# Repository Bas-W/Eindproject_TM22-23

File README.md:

# eindprojectTM22_23
In dit project maken we een line following robot.
Je vindt in deze repository de bestanden om met een 3D printer de nodige stukken te vervaardigen alsook de code en een pdf waarin uitgelegd wordt hoe de hardware moet worden gemonteerd.

Hoe de server moet worden opgezet wordt niet uitgelegd.

Het project maakt gebruik van MQTT om te communiceren tussen de server en de robot. De robot stuurt data naar de server via MQTT, deze data wordt dan in een influxDB database gezet door een python script. De data kan dan weergegeven worden in een Grafana webpagina. De robot kan ook bediend worden vanuit de webpagina via MQTT berichten.

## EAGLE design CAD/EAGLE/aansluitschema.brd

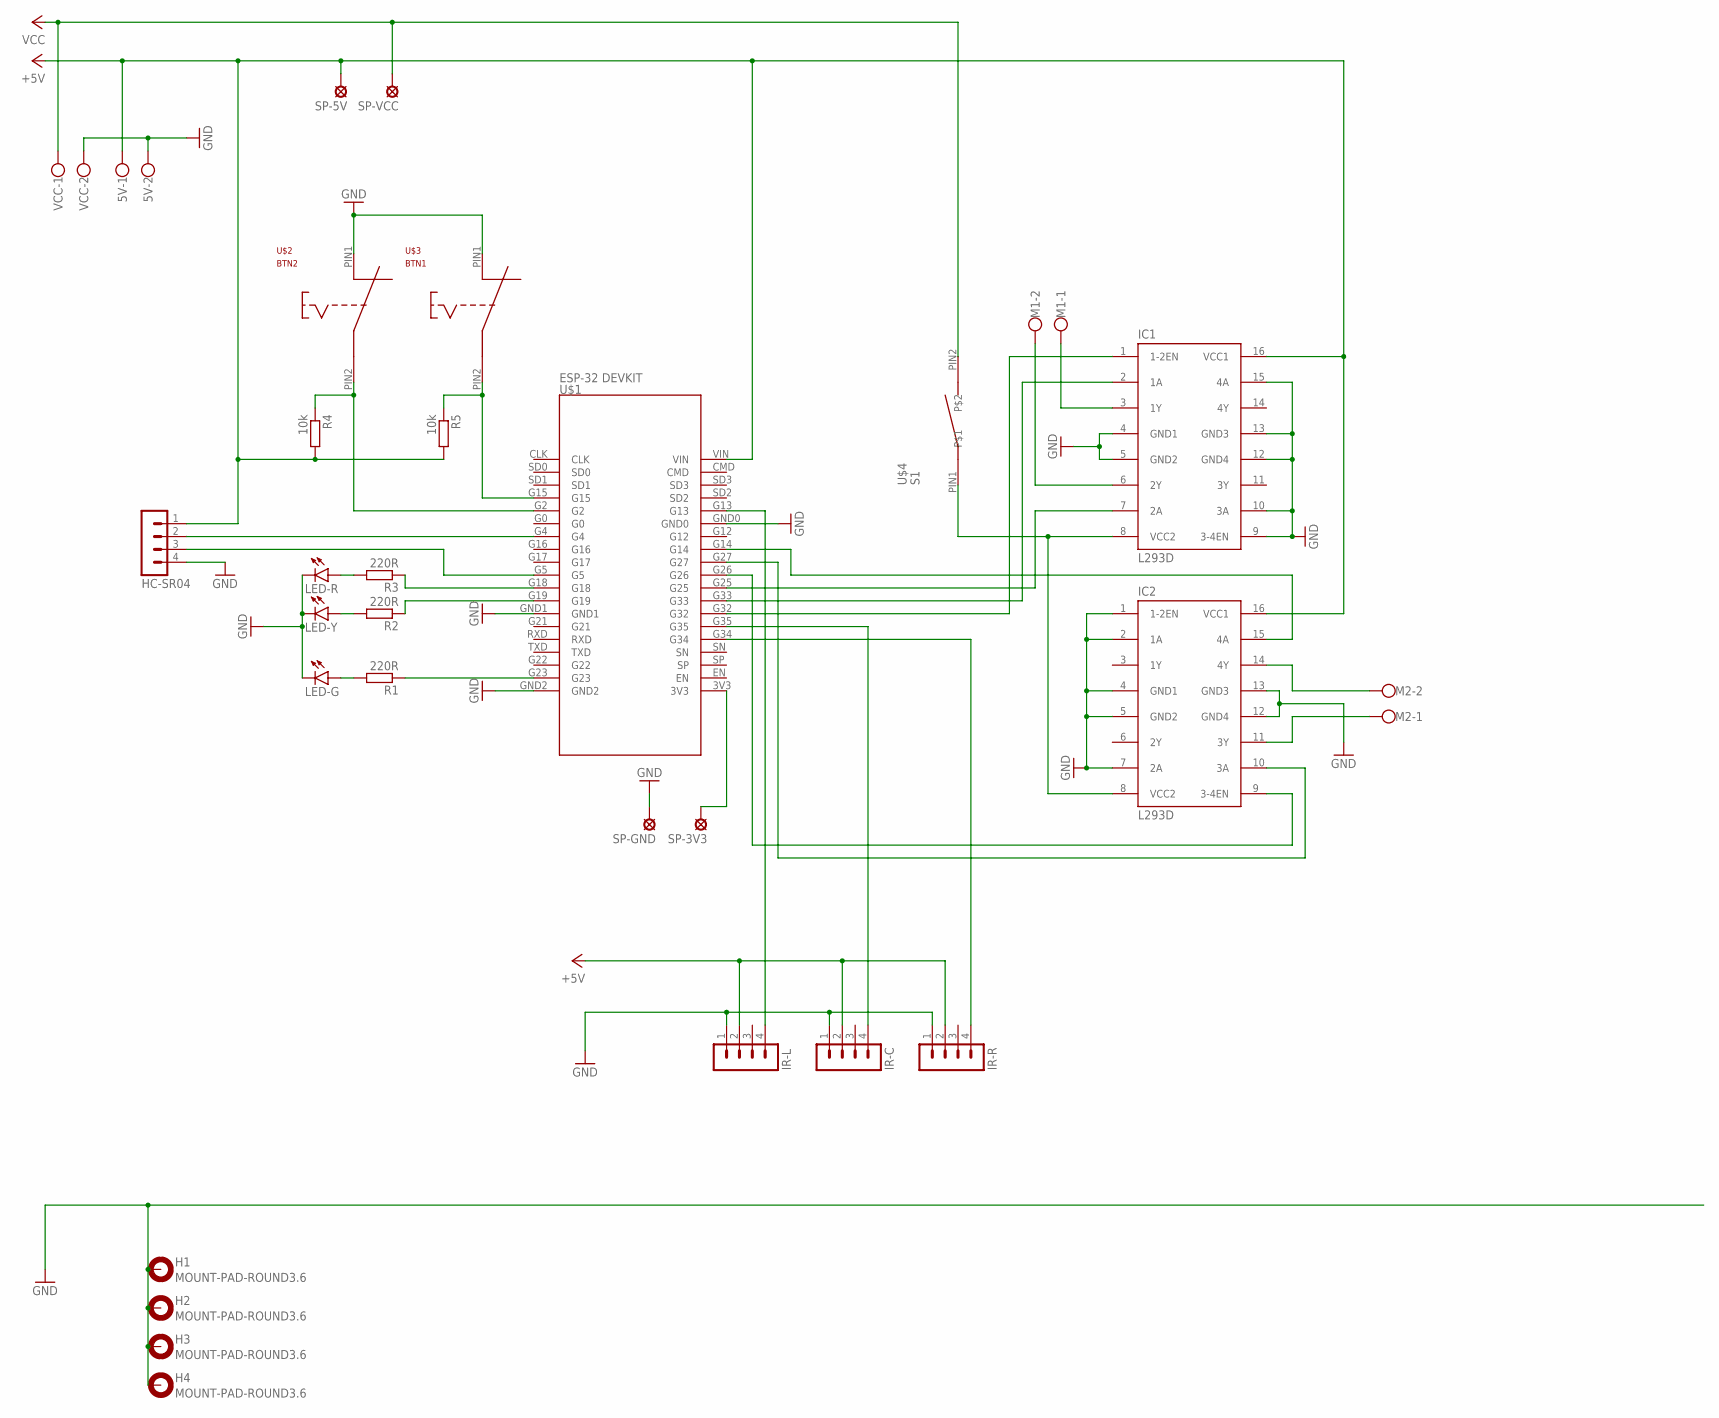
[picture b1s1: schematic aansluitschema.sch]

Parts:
5V: W237-102
H1, H2, H3, H4: MOUNT-PAD-ROUND3.6; 3,6-PAD
HC-SR04: MA04-1
IC1, IC2: L293D; DIL16
IR-C: MA04-1
IR-L: MA04-1
IR-R: MA04-1
LED-G: LED5MM
LED-R: LED5MM
LED-Y: LED5MM
M1, M2: W237-102
R1, R2, R3: 220R; 0207/10
R4, R5: 10k; 0207/10
SP-3V3, SP-5V: LSP10
SP-GND: LSP10
SP-VCC: LSP10
U$1: ESP-32 DEVKIT; ESP-32_DEVKIT
U$2: BTN2; PUSHBUTTON
U$3: BTN1; PUSHBUTTON
U$4: S1; SWITCH
VCC: W237-102

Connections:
+5V: 5V.1, HC-SR04.1, IC1.16 (VCC1), IC2.16 (VCC1), IR-C.2, IR-L.2, IR-R.2, R4.2, R5.2, SP-5V.MP, U$1.VIN
GND: 5V.2, H1.B3,6, H2.B3,6, H3.B3,6, H4.B3,6, HC-SR04.4, IC1.4 (GND1), IC1.5 (GND2), IC1.9 (3-4EN), IC1.10 (3A), IC1.12 (GND4), IC1.13 (GND3), IC1.15 (4A), IC2.1 (1-2EN), IC2.2 (1A), IC2.4 (GND1), IC2.5 (GND2), IC2.7 (2A), IC2.12 (GND4), IC2.13 (GND3), IR-C.1, IR-L.1, IR-R.1, LED-G.K (C), LED-R.K (C), LED-Y.K (C), SP-GND.MP, U$1.GND0, U$1.GND1, U$1.GND2, U$2.PIN1, U$3.PIN1, VCC.2
unnamed: IC1.8 (VCC2), IC2.8 (VCC2), U$4.PIN1
unnamed: LED-G.A, R1.2
unnamed: LED-Y.A, R2.2
unnamed: LED-R.A, R3.2
unnamed: R2.1, U$1.G19
unnamed: R3.1, U$1.G18
unnamed: R1.1, U$1.G23
unnamed: IR-R.4, U$1.G34
unnamed: IR-C.4, U$1.G35
unnamed: IR-L.4, U$1.G13
unnamed: HC-SR04.3, U$1.G5
unnamed: HC-SR04.2, U$1.G4
unnamed: R4.1, U$1.G2, U$2.PIN2
unnamed: R5.1, U$1.G15, U$3.PIN2
unnamed: IC1.3 (1Y), M1.1
unnamed: IC1.6 (2Y), M1.2
unnamed: IC2.11 (3Y), M2.1
unnamed: IC2.14 (4Y), M2.2
unnamed: IC1.1 (1-2EN), U$1.G32
unnamed: IC1.2 (1A), U$1.G33
unnamed: IC1.7 (2A), U$1.G25
unnamed: IC2.9 (3-4EN), U$1.G26
unnamed: IC2.10 (3A), U$1.G27
unnamed: IC2.15 (4A), U$1.G14
unnamed: SP-3V3.MP, U$1.3V3
VCC: SP-VCC.MP, U$4.PIN2, VCC.1

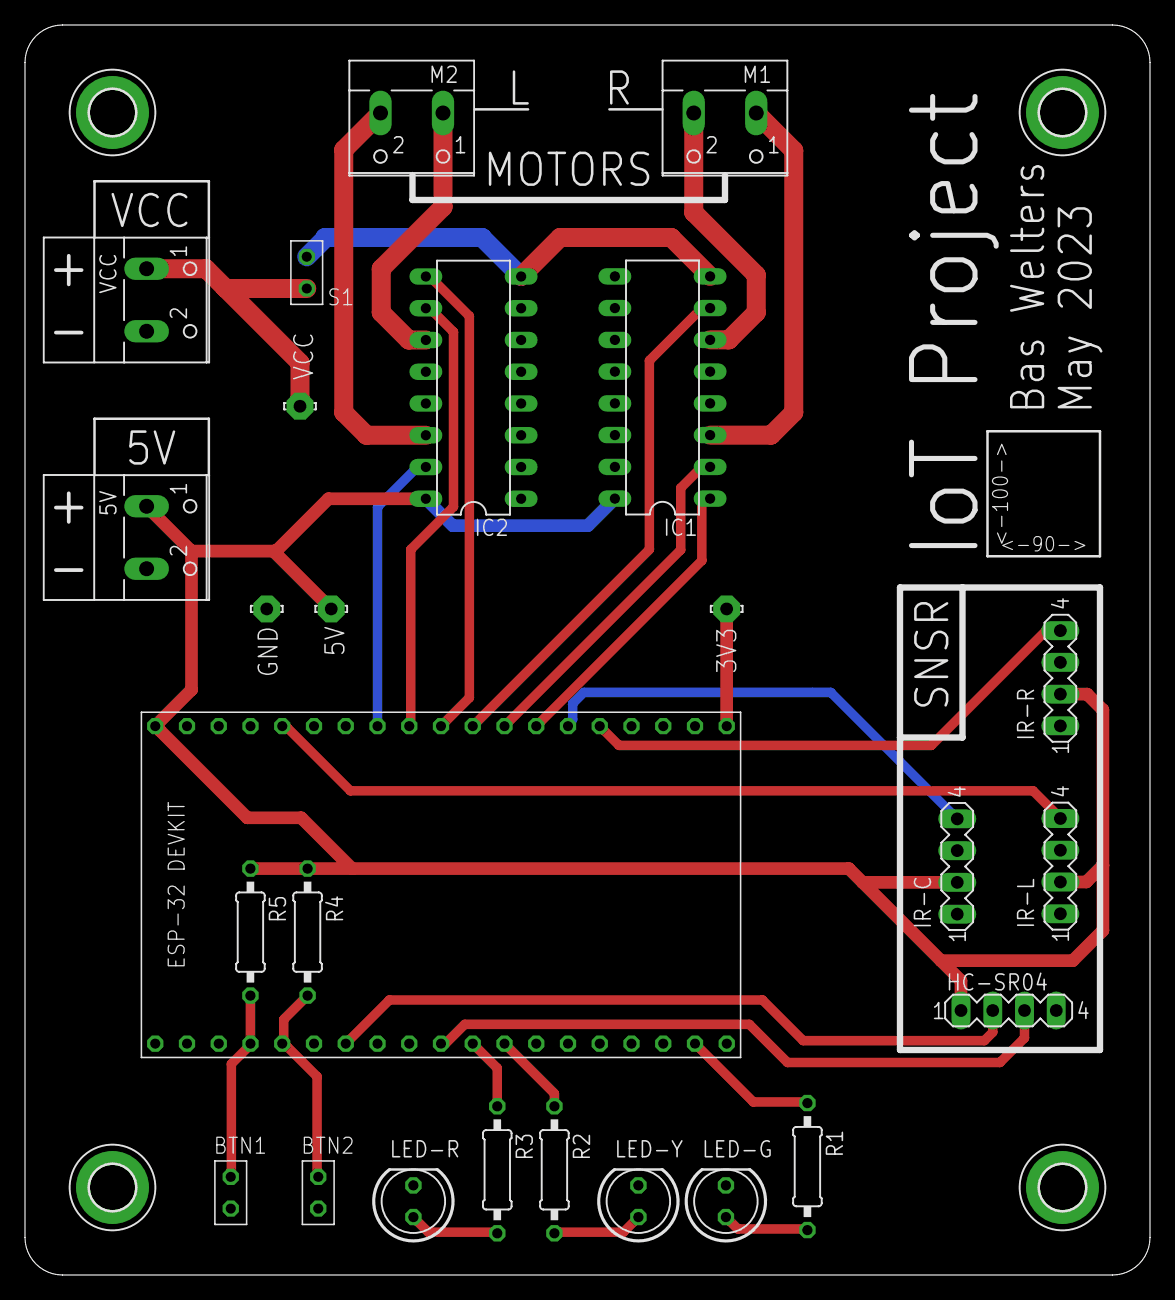
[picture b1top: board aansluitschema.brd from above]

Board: 2 copper layers, 90.0 x 100.0 mm, 30 parts (0 on the bottom side), 28 nets.

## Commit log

2023-06-02 Added all needed files
